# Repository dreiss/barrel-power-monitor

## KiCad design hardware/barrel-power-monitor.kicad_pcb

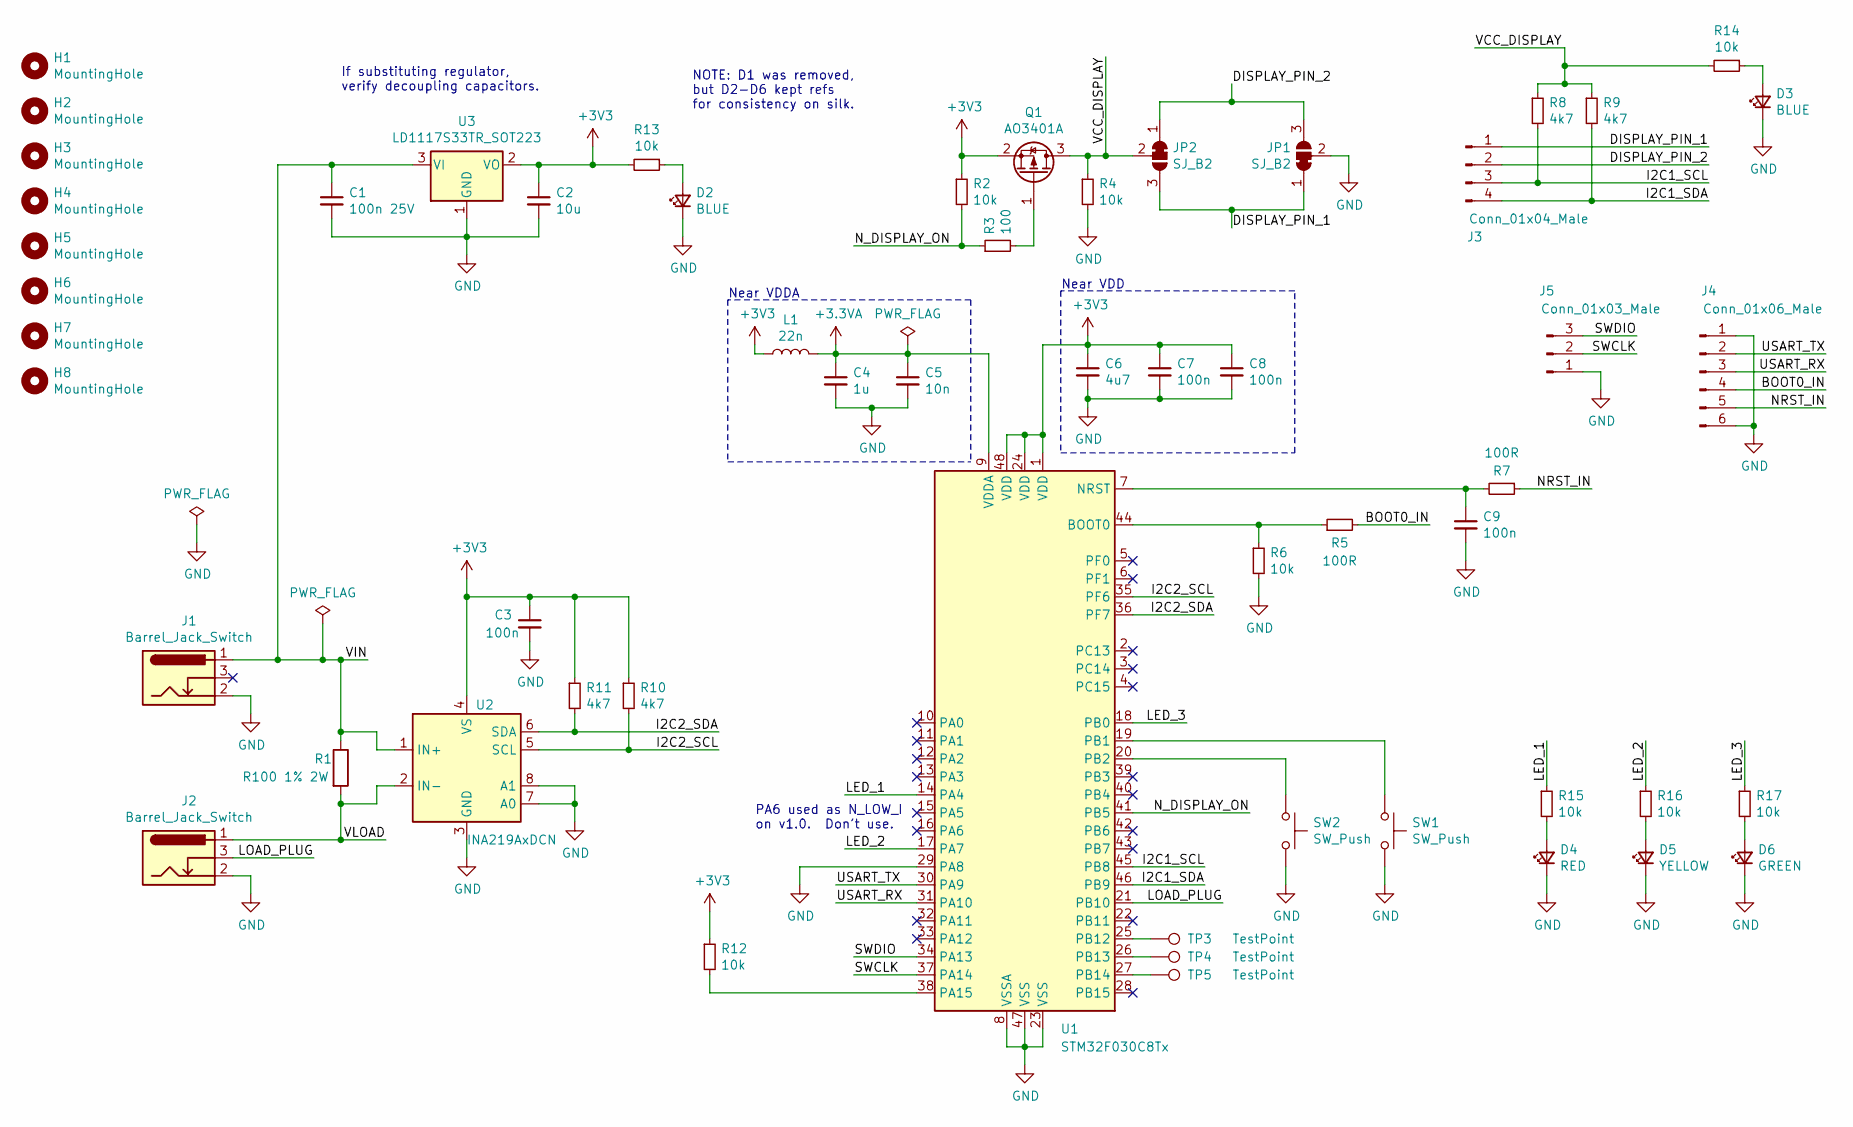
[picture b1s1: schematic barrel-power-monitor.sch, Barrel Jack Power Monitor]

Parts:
C1: 100n 25V; C_0603_1608Metric
C2: 10u; C_0603_1608Metric
C3, C7, C8, C9: 100n; C_0402_1005Metric
C4: 1u; C_0402_1005Metric
C5: 10n; C_0402_1005Metric
C6: 4u7; C_0402_1005Metric
D2, D3: BLUE; LED_0603_1608Metric; LCSC C72041
D4: RED; LED_0603_1608Metric; LCSC C2286
D5: YELLOW; LED_0603_1608Metric; LCSC C72042
D6: GREEN; LED_0603_1608Metric; LCSC C72043
H1, H2, H3, H4: MountingHole; MountingHole_2.2mm_M2
H5, H6, H7, H8: MountingHole; JLCPCB-Tooling-Hole
J1, J2: Barrel_Jack_Switch; BarrelJack_Wuerth_6941xx301002
J3: Conn_01x04_Male; PinHeader_1x04_P2.54mm_Vertical
J4: Conn_01x06_Male; PinHeader_1x06_P2.54mm_Vertical
J5: Conn_01x03_Male; PinHeader_1x03_P2.54mm_Horizontal
JP1, JP2: SJ_B2; SolderJumper-3_P1.3mm_Bridged12_RoundedPad1.0x1.5mm
L1: 22n; L_0603_1608Metric
Q1: AO3401A; SOT-23
R1: R100 1% 2W; R_2512_6332Metric; LCSC C76254
R2, R4, R6, R12: 10k; R_0402_1005Metric
R3: 100; R_0402_1005Metric
R5, R7: 100R; R_0402_1005Metric
R8, R9, R10, R11: 4k7; R_0402_1005Metric
R13, R14, R15, R16, R17: 10k; R_0603_1608Metric_Pad0.98x0.95mm_HandSolder
SW1, SW2: SW_Push; GT-TC029X-H0XX-L1N; LCSC C843669
TP3, TP4, TP5: TestPoint; TestPoint_Pad_D1.5mm
U1: STM32F030C8Tx; LQFP-48_7x7mm_P0.5mm
U2: INA219AxDCN; SOT-23-8
U3: LD1117S33TR_SOT223; SOT-223-3_TabPin2

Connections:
+3.3VA: C4.1, C5.1, L1.2, U1.9 (VDDA)
+3V3: C2.1, C3.1, C6.1, C7.1, C8.1, L1.1, Q1.2 (S), R2.1, R10.1, R11.1, R12.1, R13.2, U1.1 (VDD), U1.24 (VDD), U1.48 (VDD), U2.4 (VS), U3.2 (VO)
/BOOT0_IN: J4.4, R5.2
/DISPLAY_PIN_1: J3.1, JP1.1 (A), JP2.3 (B)
/DISPLAY_PIN_2: J3.2, JP1.3 (B), JP2.1 (A)
/I2C1_SCL: J3.3, R8.2, U1.45 (PB8)
/I2C1_SDA: J3.4, R9.2, U1.46 (PB9)
/I2C2_SCL: R10.2, U1.35 (PF6), U2.5 (SCL)
/I2C2_SDA: R11.2, U1.36 (PF7), U2.6 (SDA)
/LED_1: R15.1, U1.14 (PA4)
/LED_2: R16.1, U1.17 (PA7)
/LED_3: R17.1, U1.18 (PB0)
/LOAD_PLUG: J2.3, U1.21 (PB10)
/NRST_IN: J4.5, R7.1
/N_DISPLAY_ON: R2.2, R3.1, U1.41 (PB5)
/SWCLK: J5.2, U1.37 (PA14)
/SWDIO: J5.3, U1.34 (PA13)
/USART_RX: J4.3, U1.31 (PA10)
/USART_TX: J4.2, U1.30 (PA9)
/VCC_DISPLAY: JP2.2 (C), Q1.3 (D), R4.1, R8.1, R9.1, R14.2
/VIN: C1.1, J1.1, R1.1, U2.1 (IN+), U3.3 (VI)
/VLOAD: J2.1, R1.2, U2.2 (IN-)
GND: C1.2, C2.2, C3.2, C4.2, C5.2, C6.2, C7.2, C8.2, C9.2, D2.1 (K), D3.1 (K), D4.1 (K), D5.1 (K), D6.1 (K), J1.2, J2.2, J4.1, J4.6, J5.1, JP1.2 (C), R4.2, R6.2, SW1.2, SW2.2, U1.8 (VSSA), U1.23 (VSS), U1.29 (PA8), U1.47 (VSS), U2.3 (GND), U2.7 (A0), U2.8 (A1), U3.1 (GND)
unnamed: C9.1, R7.2, U1.7 (NRST)
unnamed: D2.2 (A), R13.1
unnamed: D3.2 (A), R14.1
unnamed: D4.2 (A), R15.2
unnamed: D5.2 (A), R16.2
unnamed: D6.2 (A), R17.2
unnamed: Q1.1 (G), R3.2
unnamed: R5.1, R6.1, U1.44 (BOOT0)
unnamed: R12.2, U1.38 (PA15)
unnamed: SW1.1, U1.19 (PB1)
unnamed: SW2.1, U1.20 (PB2)
unnamed: TP3.1, U1.25 (PB12)
unnamed: TP4.1, U1.26 (PB13)
unnamed: TP5.1, U1.27 (PB14)

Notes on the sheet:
Near VDD
Near VDDA
If substituting regulator, verify decoupling capacitors.
PA6 used as N_LOW_I on v1.0. Don't use.
NOTE: D1 was removed, but D2-D6 kept refs for consistency on silk.

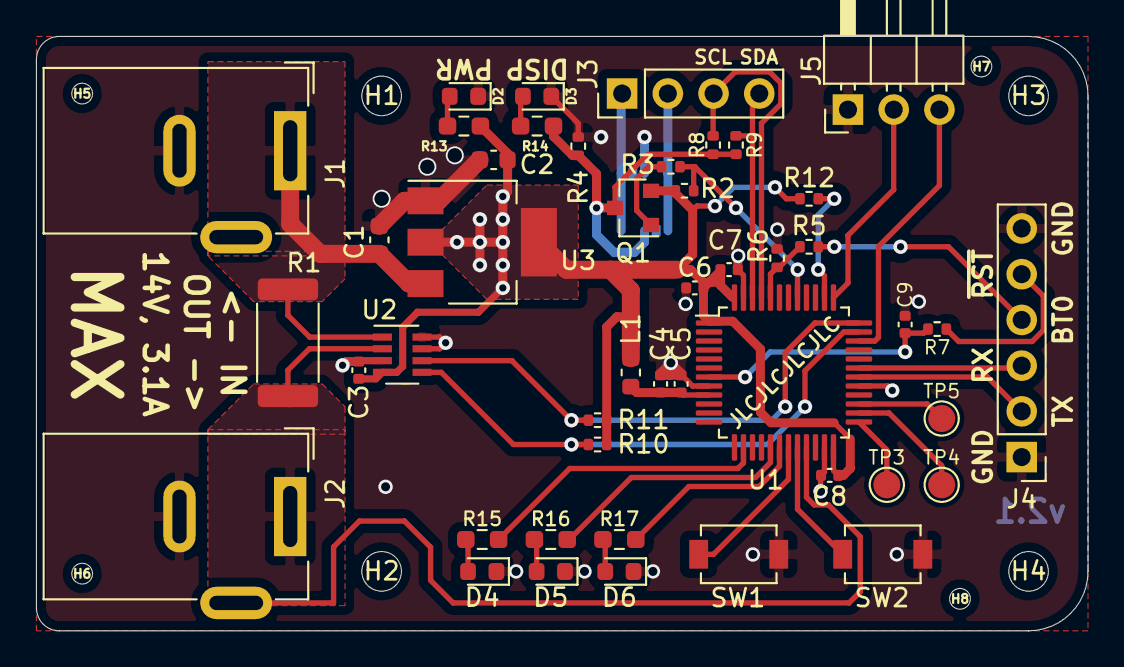
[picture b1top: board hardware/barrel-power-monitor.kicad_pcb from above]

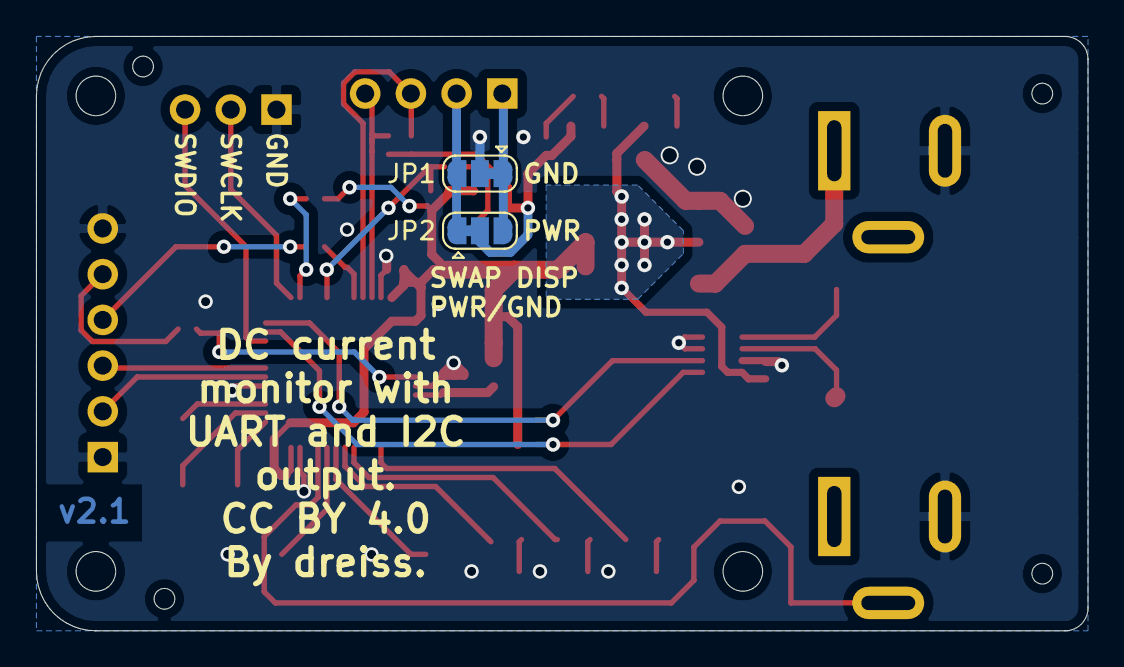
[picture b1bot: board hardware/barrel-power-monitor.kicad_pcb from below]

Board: 2 copper layers, 58.4 x 33.0 mm, 56 parts (2 on the bottom side), 37 nets.

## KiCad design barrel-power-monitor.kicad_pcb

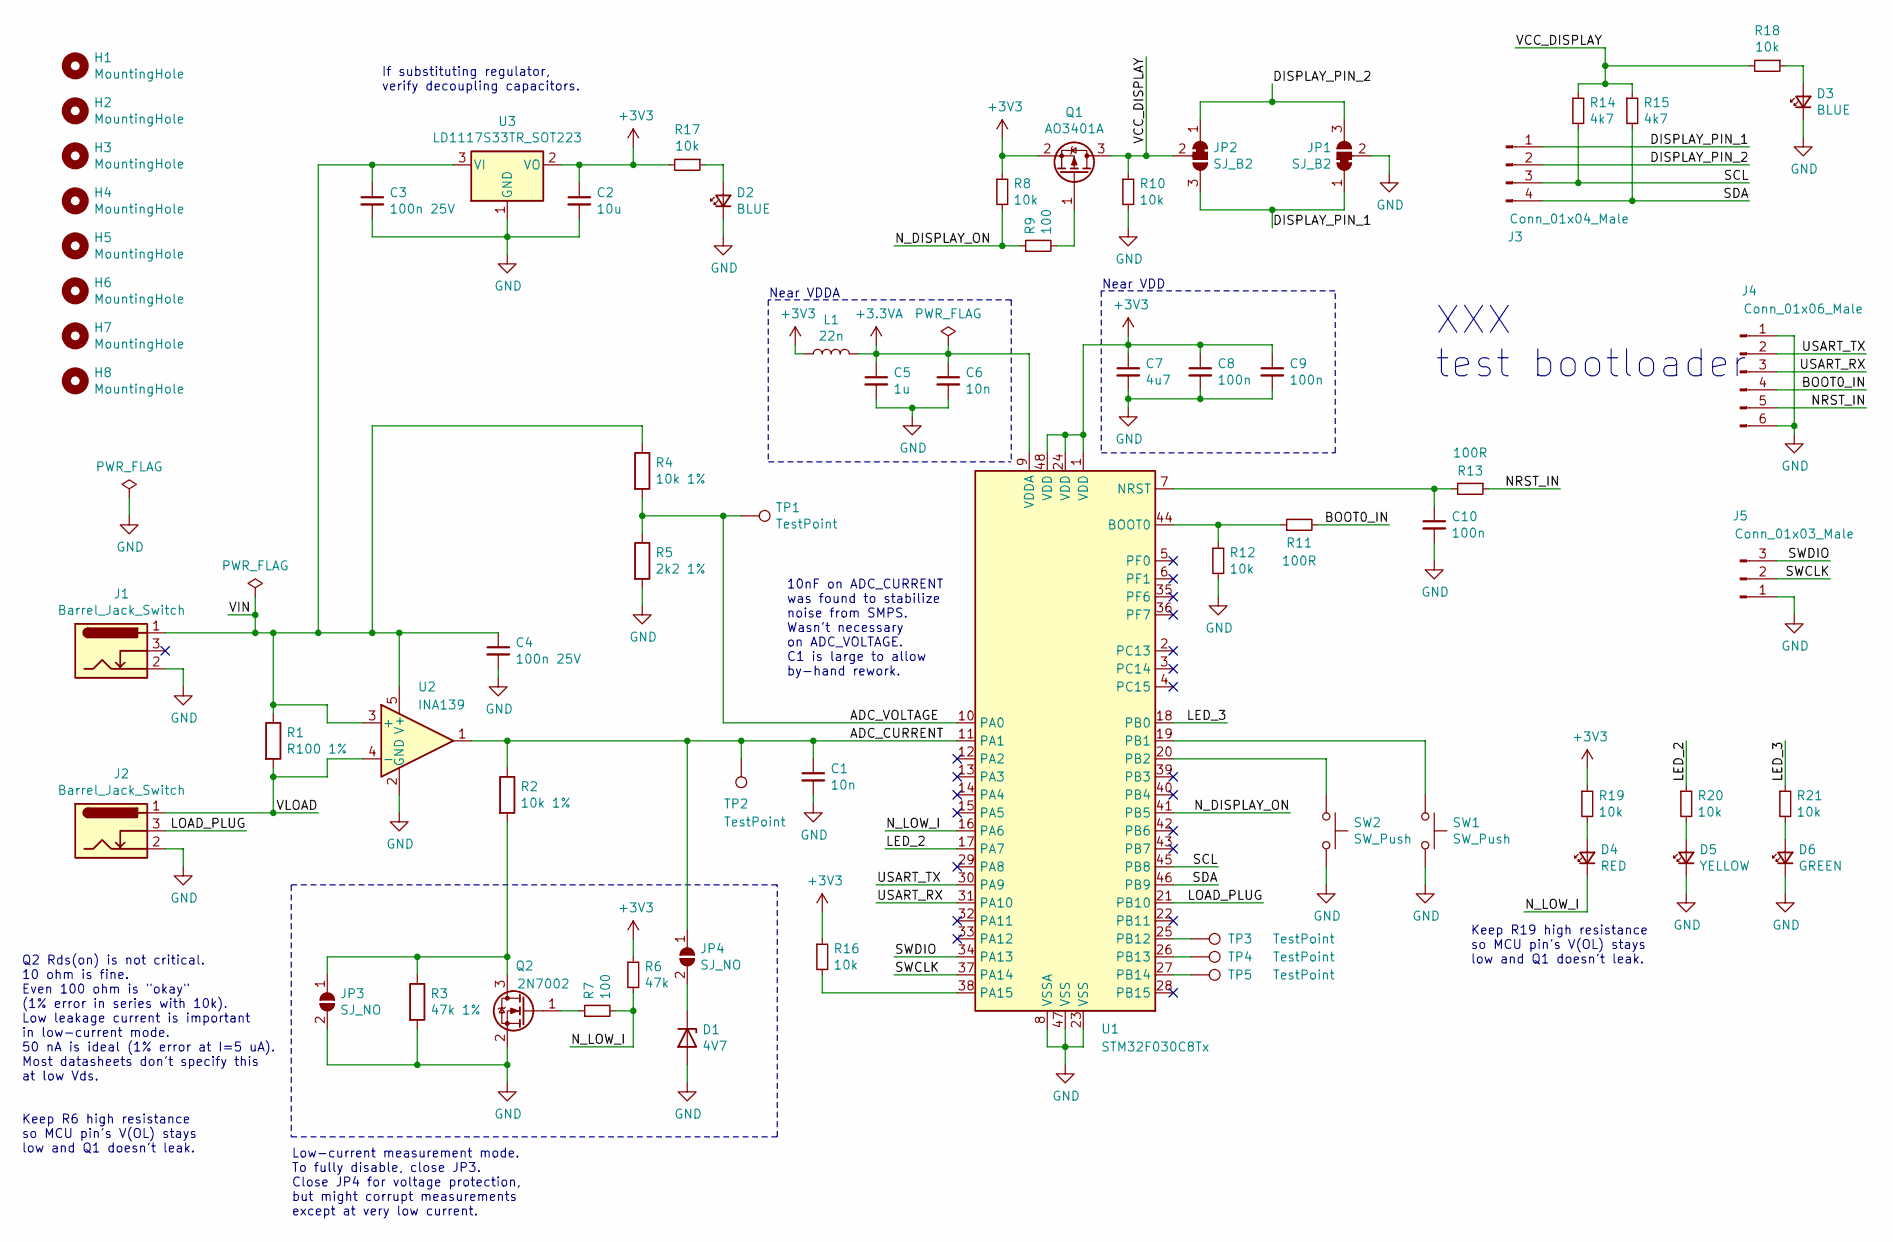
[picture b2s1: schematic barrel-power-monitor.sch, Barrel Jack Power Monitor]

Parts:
C1: 10n; C_0805_2012Metric_Pad1.18x1.45mm_HandSolder
C2: 10u; C_0603_1608Metric
C3, C4: 100n 25V; C_0603_1608Metric
C5: 1u; C_0402_1005Metric
C6: 10n; C_0402_1005Metric
C7: 4u7; C_0402_1005Metric
C8, C9, C10: 100n; C_0402_1005Metric
D1: 4V7; D_MiniMELF
D2, D3: BLUE; LED_0603_1608Metric; LCSC C72041
D4: RED; LED_0603_1608Metric; LCSC C2286
D5: YELLOW; LED_0603_1608Metric; LCSC C72042
D6: GREEN; LED_0603_1608Metric; LCSC C72043
H1, H2, H3, H4: MountingHole; MountingHole_2.2mm_M2
H5, H6, H7, H8: MountingHole; JLCPCB-Tooling-Hole
J1, J2: Barrel_Jack_Switch; BarrelJack_Wuerth_6941xx301002
J3: Conn_01x04_Male; PinHeader_1x04_P2.54mm_Vertical
J4: Conn_01x06_Male; PinHeader_1x06_P2.54mm_Vertical
J5: Conn_01x03_Male; PinHeader_1x03_P2.54mm_Horizontal
JP1, JP2: SJ_B2; SolderJumper-3_P1.3mm_Bridged12_RoundedPad1.0x1.5mm
JP3, JP4: SJ_NO; SolderJumper-2_P1.3mm_Open_RoundedPad1.0x1.5mm
L1: 22n; L_0603_1608Metric
Q1: AO3401A; SOT-23
Q2: 2N7002; SOT-23
R1: R100 1%; R_2512_6332Metric; LCSC C76254
R2, R4: 10k 1%; R_0402_1005Metric
R3: 47k 1%; R_0402_1005Metric
R5: 2k2 1%; R_0402_1005Metric
R6: 47k; R_0402_1005Metric
R7, R9: 100; R_0402_1005Metric
R8, R10, R12, R16: 10k; R_0402_1005Metric
R11, R13: 100R; R_0402_1005Metric
R14, R15: 4k7; R_0402_1005Metric
R17, R18, R19, R20, R21: 10k; R_0603_1608Metric_Pad0.98x0.95mm_HandSolder
SW1, SW2: SW_Push; GT-TC029X-H0XX-L1N; LCSC C843669
TP1, TP2, TP3, TP4, TP5: TestPoint; TestPoint_Pad_D1.5mm
U1: STM32F030C8Tx; LQFP-48_7x7mm_P0.5mm
U2: INA139; SOT-23-5
U3: LD1117S33TR_SOT223; SOT-223-3_TabPin2

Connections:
+3.3VA: C5.1, C6.1, L1.2, U1.9 (VDDA)
+3V3: C2.1, C7.1, C8.1, C9.1, L1.1, Q1.2 (S), R6.1, R8.1, R16.1, R17.2, R19.1, U1.1 (VDD), U1.24 (VDD), U1.48 (VDD), U3.2 (VO)
/ADC_CURRENT: C1.1, JP4.1 (A), R2.1, TP2.1, U1.11 (PA1), U2.1
/ADC_VOLTAGE: R4.2, R5.1, TP1.1, U1.10 (PA0)
/BOOT0_IN: J4.4, R11.2
/DISPLAY_PIN_1: J3.1, JP1.1 (A), JP2.3 (B)
/DISPLAY_PIN_2: J3.2, JP1.3 (B), JP2.1 (A)
/LED_2: R20.1, U1.17 (PA7)
/LED_3: R21.1, U1.18 (PB0)
/LOAD_PLUG: J2.3, U1.21 (PB10)
/NRST_IN: J4.5, R13.1
/N_DISPLAY_ON: R8.2, R9.1, U1.41 (PB5)
/N_LOW_I: D4.1 (K), R6.2, R7.2, U1.16 (PA6)
/SCL: J3.3, R14.2, U1.45 (PB8)
/SDA: J3.4, R15.2, U1.46 (PB9)
/SWCLK: J5.2, U1.37 (PA14)
/SWDIO: J5.3, U1.34 (PA13)
/USART_RX: J4.3, U1.31 (PA10)
/USART_TX: J4.2, U1.30 (PA9)
/VCC_DISPLAY: JP2.2 (C), Q1.3 (D), R10.1, R14.1, R15.1, R18.2
/VIN: C3.1, C4.1, J1.1, R1.1, R4.1, U2.3 (+), U2.5 (V+), U3.3 (VI)
/VLOAD: J2.1, R1.2, U2.4 (-)
GND: C1.2, C2.2, C3.2, C4.2, C5.2, C6.2, C7.2, C8.2, C9.2, C10.2, D1.2 (A), D2.1 (K), D3.1 (K), D5.1 (K), D6.1 (K), J1.2, J2.2, J4.1, J4.6, J5.1, JP1.2 (C), JP3.2 (B), Q2.2 (S), R3.2, R5.2, R10.2, R12.2, SW1.2, SW2.2, U1.8 (VSSA), U1.23 (VSS), U1.47 (VSS), U2.2 (GND), U3.1 (GND)
unnamed: C10.1, R13.2, U1.7 (NRST)
unnamed: D1.1 (K), JP4.2 (B)
unnamed: D2.2 (A), R17.1
unnamed: D3.2 (A), R18.1
unnamed: D4.2 (A), R19.2
unnamed: D5.2 (A), R20.2
unnamed: D6.2 (A), R21.2
unnamed: JP3.1 (A), Q2.3 (D), R2.2, R3.1
unnamed: Q1.1 (G), R9.2
unnamed: Q2.1 (G), R7.1
unnamed: R11.1, R12.1, U1.44 (BOOT0)
unnamed: R16.2, U1.38 (PA15)
unnamed: SW1.1, U1.19 (PB1)
unnamed: SW2.1, U1.20 (PB2)
unnamed: TP3.1, U1.25 (PB12)
unnamed: TP4.1, U1.26 (PB13)
unnamed: TP5.1, U1.27 (PB14)

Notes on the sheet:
Near VDD
Low-current measurement mode. To fully disable, close JP3. Close JP4 for voltage protection, but might corrupt measurements except at very low current.
Q2 Rds(on) is not critical. 10 ohm is fine. Even 100 ohm is "okay" (1% error in series with 10k). Low leakage current is important in low-current mode. 50 nA is ideal (1% error at I=5 uA). Most datasheets don't specify this at low Vds.
Near VDDA
If substituting regulator, verify decoupling capacitors.
Keep R19 high resistance so MCU pin's V(OL) stays low and Q1 doesn't leak.
10nF on ADC_CURRENT was found to stabilize noise from SMPS. Wasn't necessary on ADC_VOLTAGE. C1 is large to allow by-hand rework.
XXX test bootloader
Keep R6 high resistance so MCU pin's V(OL) stays low and Q1 doesn't leak.

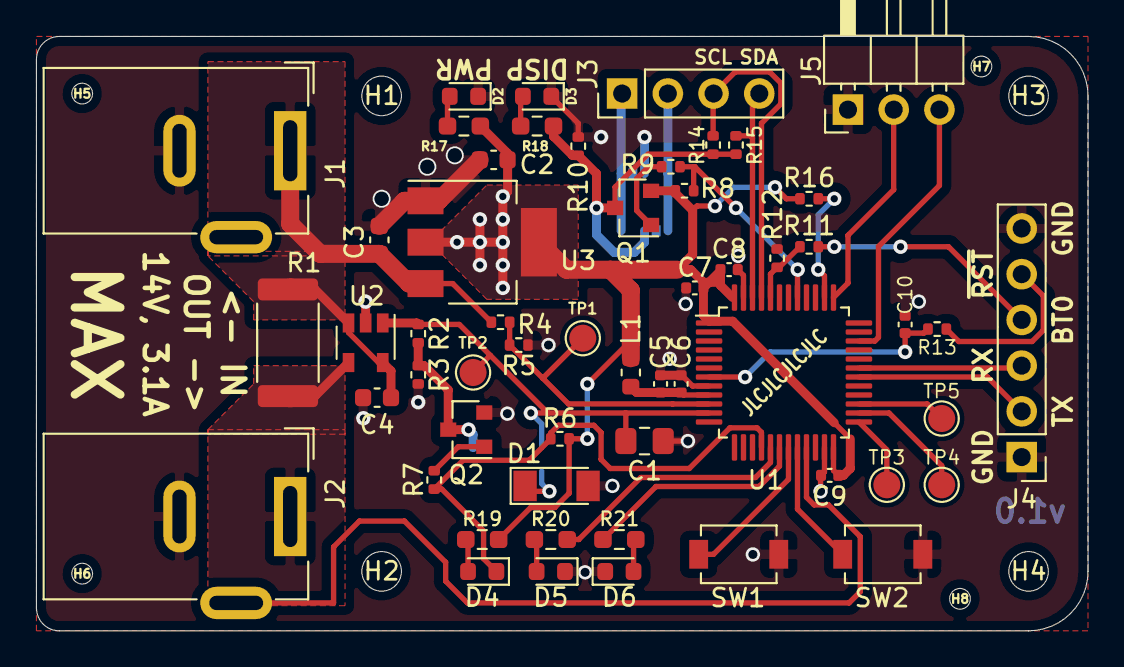
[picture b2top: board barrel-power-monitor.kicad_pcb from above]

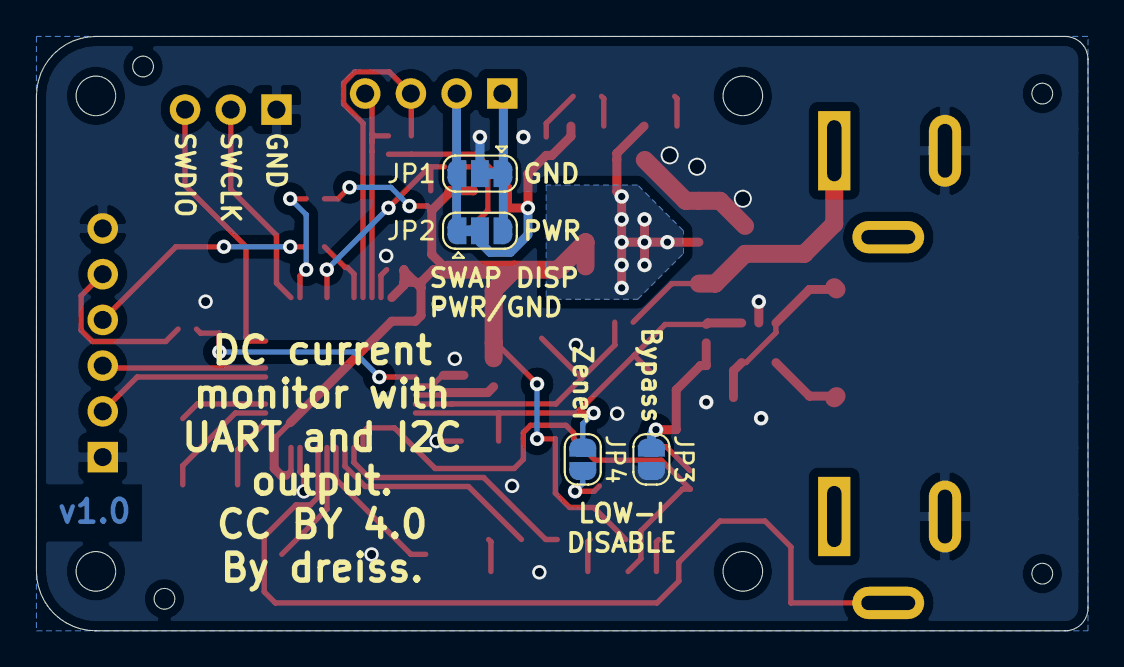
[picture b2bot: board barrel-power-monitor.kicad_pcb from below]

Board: 2 copper layers, 58.4 x 33.0 mm, 67 parts (4 on the bottom side), 40 nets.

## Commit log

2021-02-16 Stub initial commit
2021-02-19 Initial version for external review
2021-02-19 Initial hardware version for external review
2021-02-19 Add pictures and pdf
2021-10-11 fix-silk-d6

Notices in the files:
barrel-power-monitor.kicad_pcb:
License: CC BY 4.0
CC BY 4.0
